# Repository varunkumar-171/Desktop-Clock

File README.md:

# Desktop-Clock

| PCB - Back View | PCB - Front View |
| :---: | :---: |
|  |  |

| Clock - Front View | Clock - Side View |
| :---: | :---: |
|  |  |

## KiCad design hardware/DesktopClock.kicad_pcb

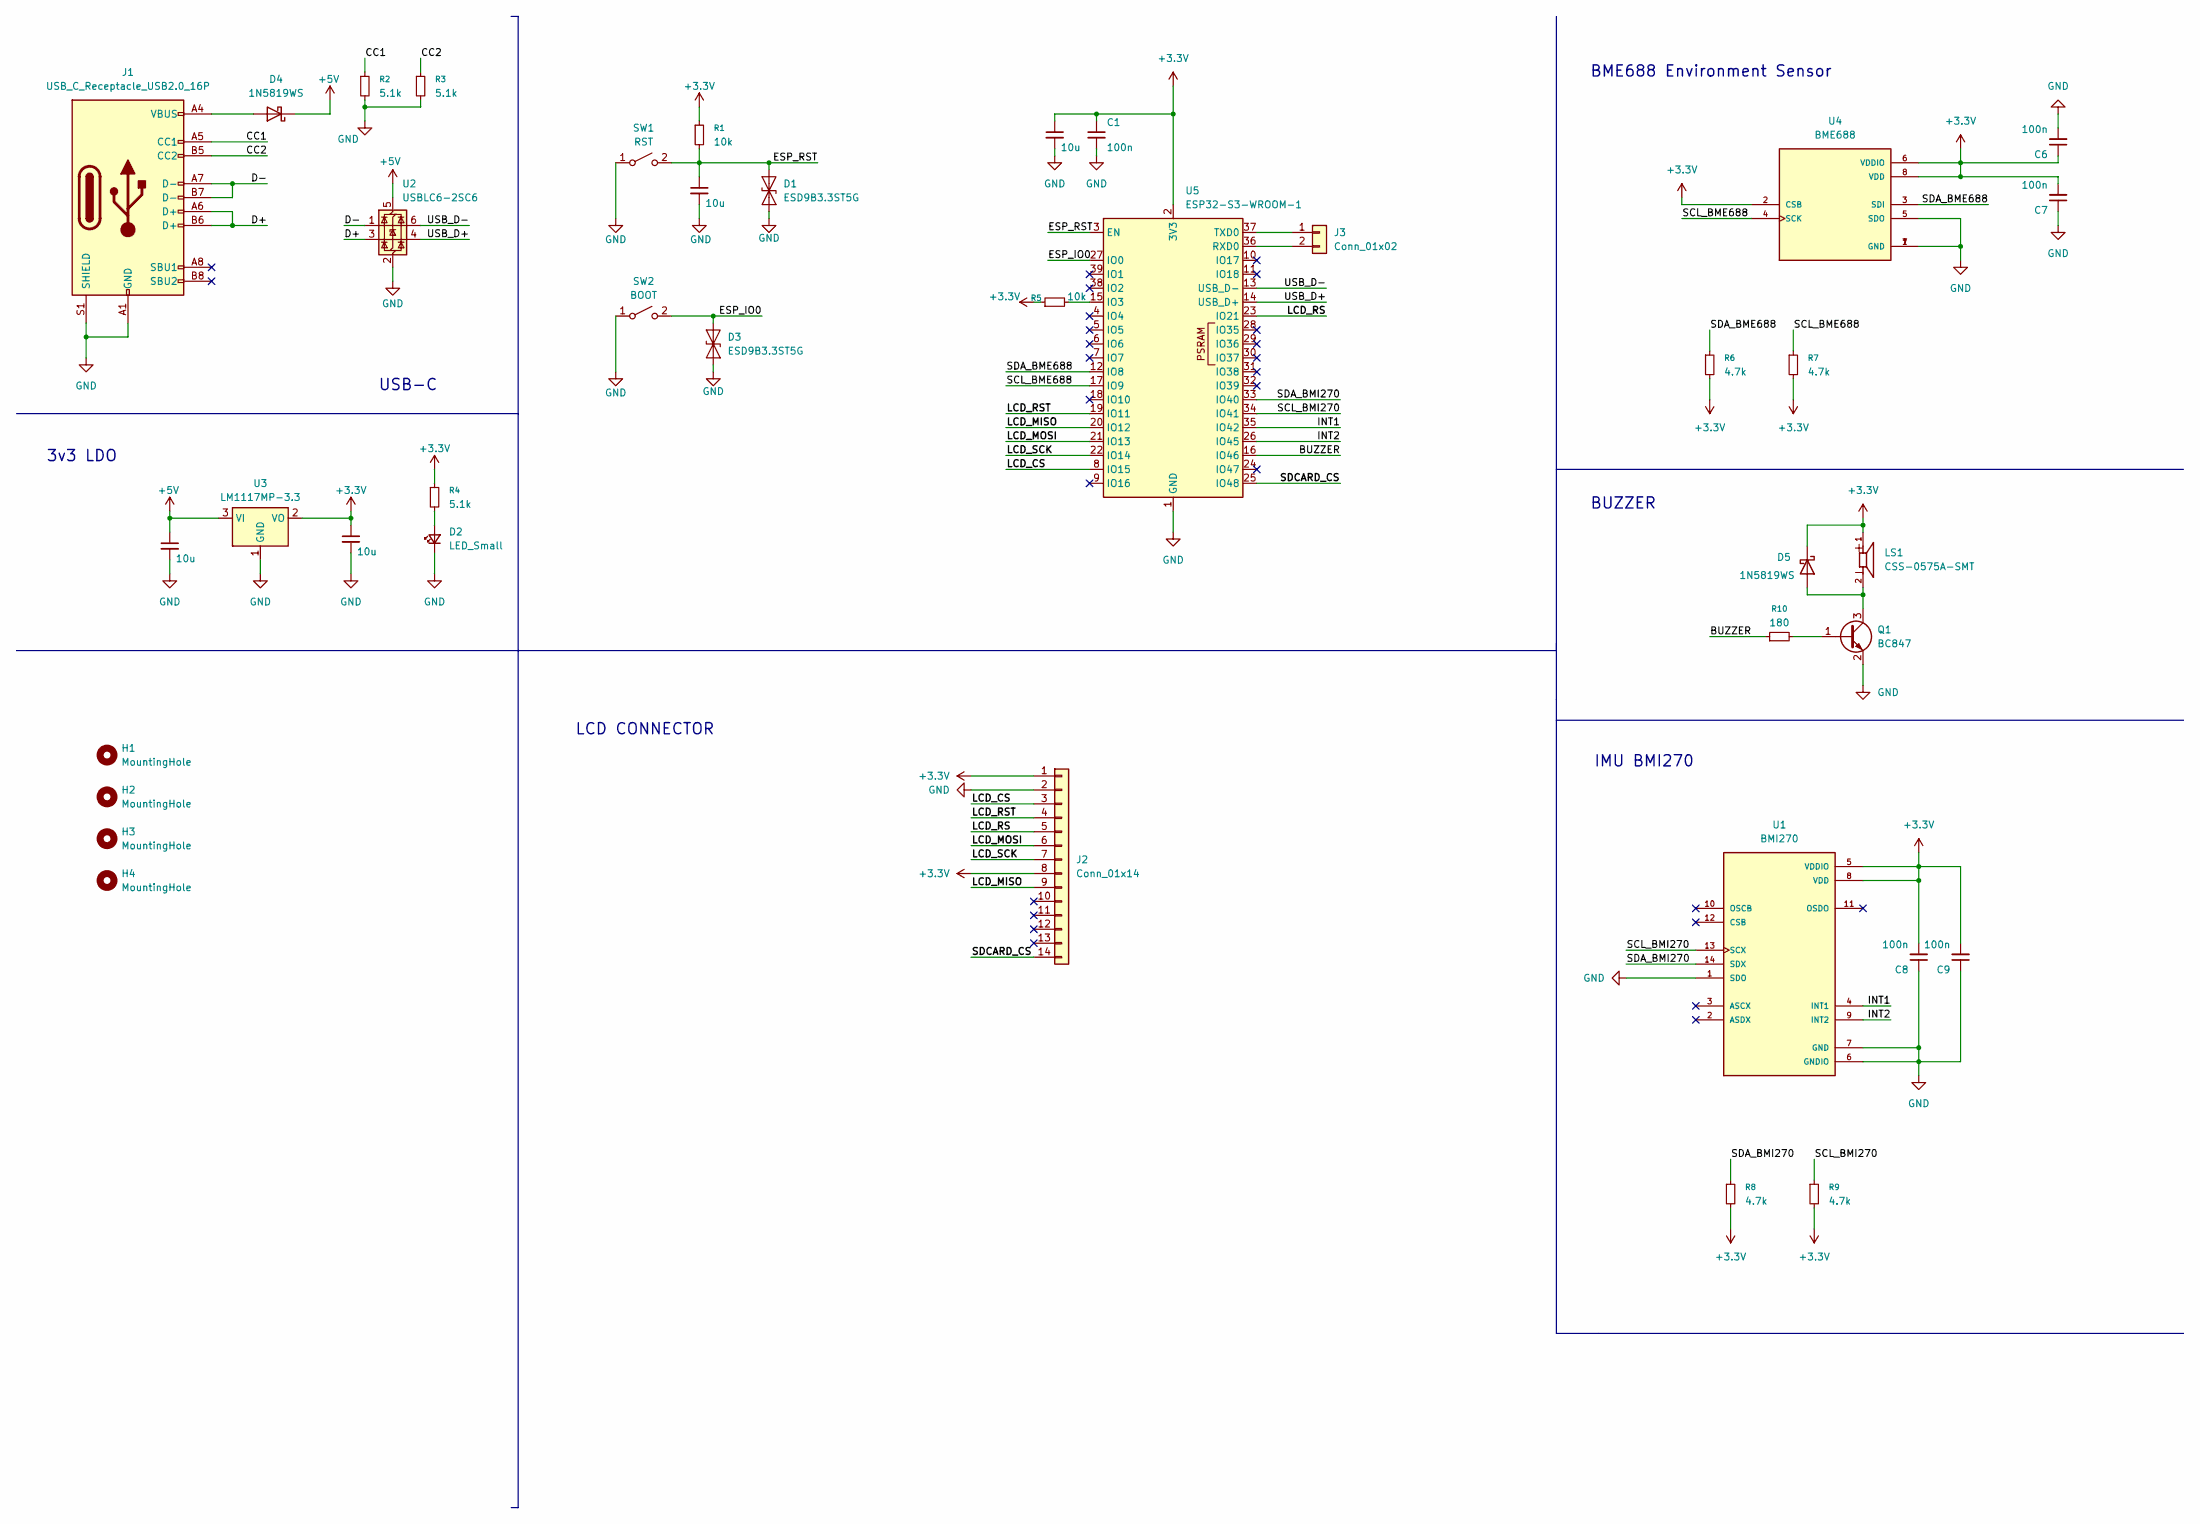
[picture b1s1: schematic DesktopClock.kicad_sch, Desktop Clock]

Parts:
C1, C6, C7, C8, C9: 100n; C_0603_1608Metric_Pad1.08x0.95mm_HandSolder
C2, C3, C4, C5: 10u; C_0603_1608Metric_Pad1.08x0.95mm_HandSolder
D1, D3: ESD9B3.3ST5G; D_SOD-923
D2: LED_Small; LED_0805_2012Metric_Pad1.15x1.40mm_HandSolder
D4, D5: 1N5819WS; D_SOD-323
H1, H2, H3, H4: MountingHole; MountingHole_3.2mm_M3
J1: USB_C_Receptacle_USB2.0_16P; USB_C_Receptacle_GCT_USB4105-xx-A_16P_TopMnt_Horizontal
J2: Conn_01x14; Amphenol_F32Q-1A7x1-11014_1x14-1MP_P0.5mm_Horizontal
J3: Conn_01x02; PinHeader_1x02_P2.54mm_Horizontal
LS1: CSS-0575A-SMT; CUI_CSS-0575A-SMT
Q1: BC847; SOT-23_Handsoldering
R1, R5: 10k; R_0603_1608Metric_Pad0.98x0.95mm_HandSolder
R2, R3, R4: 5.1k; R_0603_1608Metric_Pad0.98x0.95mm_HandSolder
R6, R7, R8, R9: 4.7k; R_0603_1608Metric_Pad0.98x0.95mm_HandSolder
R10: 180; R_0603_1608Metric_Pad0.98x0.95mm_HandSolder
SW1: RST; SW_SPST_B3U-1000P
SW2: BOOT; SW_SPST_B3U-1000P
U1: BMI270; XDCR_BMI270
U2: USBLC6-2SC6; SOT-23-6
U3: LM1117MP-3.3; SOT-223-3_TabPin2
U4: BME688; IC_BME688; PARTREV 1.0
U5: ESP32-S3-WROOM-1

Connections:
+3.3V: C1.1, C2.1, C5.1, C6.1, C7.2, C8.2, C9.2, D5.1 (K), J2.1, J2.8, LS1.1, R1.1, R4.1, R5.1, R6.2, R7.2, R8.2, R9.2, U1.5 (VDDIO), U1.8 (VDD), U3.2 (VO), U4.2 (CSB), U4.6 (VDDIO), U4.8 (VDD), U5.2 (3V3)
+5V: C4.1, D4.1 (K), U2.5 (VBUS), U3.3 (VI)
/BUZZER: R10.1, U5.16 (IO46)
/CC1: J1.A5 (CC1), R2.1
/CC2: J1.B5 (CC2), R3.1
/D+: J1.A6 (D+), J1.B6 (D+), U2.3 (I/O2)
/D-: J1.A7 (D-), J1.B7 (D-), U2.1 (I/O1)
/ESP_IO0: D3.2 (A2), SW2.2 (B), U5.27 (IO0)
/ESP_RST: C3.1, D1.2 (A2), R1.2, SW1.2 (B), U5.3 (EN)
/INT1: U1.4 (INT1), U5.35 (IO42)
/INT2: U1.9 (INT2), U5.26 (IO45)
/LCD_CS: J2.3, U5.8 (IO15)
/LCD_MISO: J2.9, U5.20 (IO12)
/LCD_MOSI: J2.6, U5.21 (IO13)
/LCD_RS: J2.5, U5.23 (IO21)
/LCD_RST: J2.4, U5.19 (IO11)
/LCD_SCK: J2.7, U5.22 (IO14)
/SCL_BME688: R7.1, U4.4 (SCK), U5.17 (IO9)
/SCL_BMI270: R9.1, U1.13 (SCX), U5.34 (IO41)
/SDA_BME688: R6.1, U4.3 (SDI), U5.12 (IO8)
/SDA_BMI270: R8.1, U1.14 (SDX), U5.33 (IO40)
/SDCARD_CS: J2.14, U5.25 (IO48)
/USB_D+: U2.4 (I/O2), U5.14 (USB_D+)
/USB_D-: U2.6 (I/O1), U5.13 (USB_D-)
GND: C1.2, C2.2, C3.2, C4.2, C5.2, C6.2, C7.1, C8.1, C9.1, D1.1 (A1), D2.1 (K), D3.1 (A1), J1.A1 (GND), J1.A12 (GND), J1.B1 (GND), J1.B12 (GND), J1.S1 (SHIELD), J2.2, Q1.2 (E), R2.2, R3.2, SW1.1 (A), SW2.1 (A), U1.1 (SDO), U1.6 (GNDIO), U1.7 (GND), U2.2 (GND), U3.1 (GND), U4.1 (GND), U4.5 (SDO), U4.7 (GND), U5.1 (GND), U5.40 (GND), U5.41 (GND)
unnamed: D2.2 (A), R4.2
unnamed: D4.2 (A), J1.A4 (VBUS), J1.A9 (VBUS), J1.B4 (VBUS), J1.B9 (VBUS)
unnamed: D5.2 (A), LS1.2, Q1.3 (C)
unnamed: J3.1, U5.37 (TXD0)
unnamed: J3.2, U5.36 (RXD0)
unnamed: Q1.1 (B), R10.2
unnamed: R5.2, U5.15 (IO3)

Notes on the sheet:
USB-C
IMU BMI270
BME688 Environment Sensor
LCD CONNECTOR
3v3 LDO
BUZZER

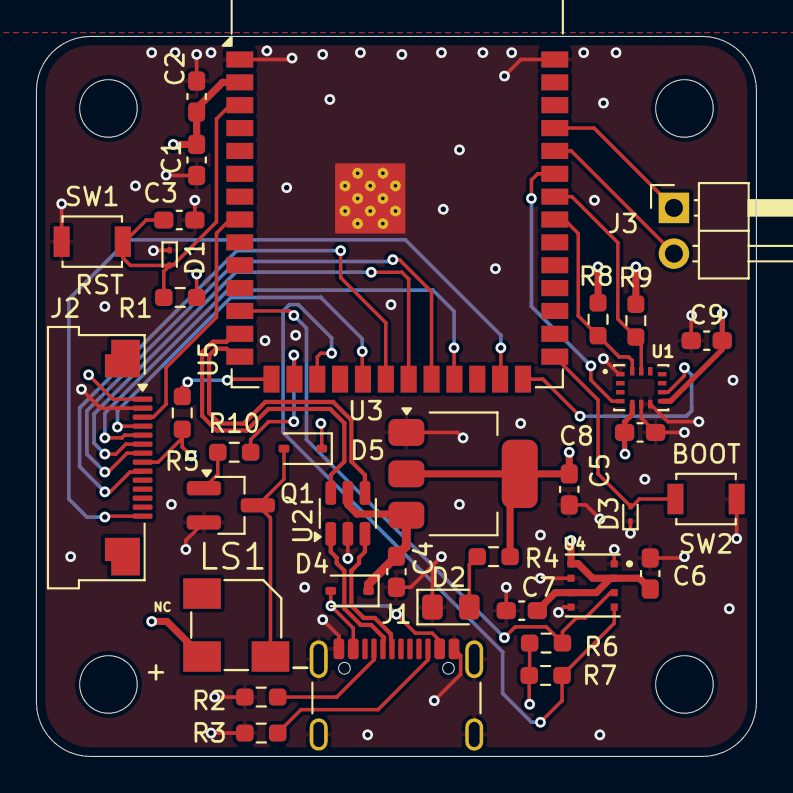
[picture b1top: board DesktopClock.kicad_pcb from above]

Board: 4 copper layers, 40.0 x 40.0 mm, 40 parts (0 on the bottom side), 32 nets.

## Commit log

2025-09-23 schem rev1.0
2025-09-23 schem ver1.0
2025-09-24 rev 3.0
2025-09-24 updated pdf
2025-09-25 Layout complete
2026-02-18 Images of the clock
